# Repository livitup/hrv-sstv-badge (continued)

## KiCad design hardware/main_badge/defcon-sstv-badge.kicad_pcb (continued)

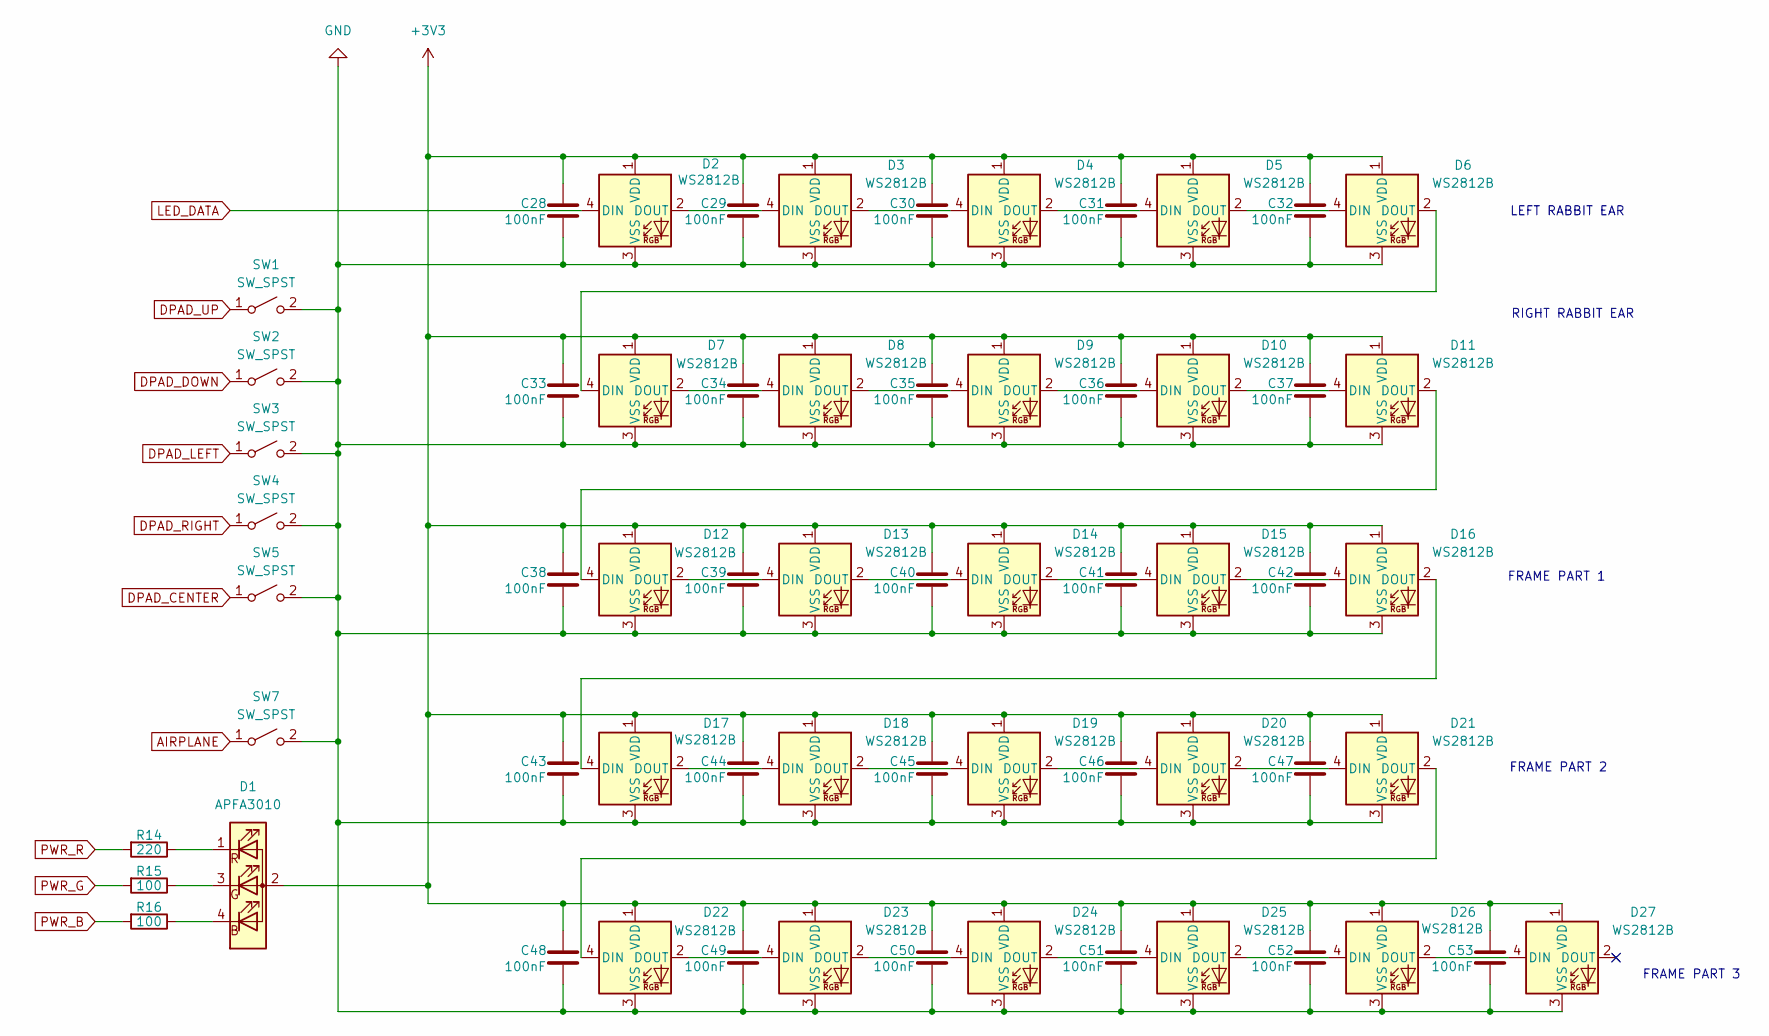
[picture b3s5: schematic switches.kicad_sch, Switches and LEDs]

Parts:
C28, C29, C30, C31, C32, C33, C34, C35, C36, C37, C38, C39, C40, C41, C42, C43, C44, C45, C46, C47, C48, C49, C50, C51, C52, C53: 100nF; C_0402_1005Metric
D1: APFA3010; LED_Kingbright_APFA3010_3x1.5mm_Horizontal
D2, D3, D4, D5, D6, D7, D8, D9, D10, D11: WS2812B; LED_WS2812B_PLCC4_5.0x5.0mm_P3.2mm
D12, D13, D14, D15, D16, D17, D18, D19, D20, D21, D22, D23, D24, D25, D26, D27: WS2812B; LED_WS2812B-2020_PLCC4_2.0x2.0mm
R14: 220; R_0603_1608Metric
R15, R16: 100; R_0603_1608Metric
SW1, SW2, SW3, SW4, SW5: SW_SPST; SW_PUSH_6mm_H5mm
SW7: SW_SPST; SW_Slide_SPDT_Angled_CK_OS102011MA1Q

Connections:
+3V3: C28.1, C29.1, C30.1, C31.1, C32.1, C33.1, C34.1, C35.1, C36.1, C37.1, C38.1, C39.1, C40.1, C41.1, C42.1, C43.1, C44.1, C45.1, C46.1, C47.1, C48.1, C49.1, C50.1, C51.1, C52.1, C53.1, D1.2 (A), D2.1 (VDD), D3.1 (VDD), D4.1 (VDD), D5.1 (VDD), D6.1 (VDD), D7.1 (VDD), D8.1 (VDD), D9.1 (VDD), D10.1 (VDD), D11.1 (VDD), D12.1 (VDD), D13.1 (VDD), D14.1 (VDD), D15.1 (VDD), D16.1 (VDD), D17.1 (VDD), D18.1 (VDD), D19.1 (VDD), D20.1 (VDD), D21.1 (VDD), D22.1 (VDD), D23.1 (VDD), D24.1 (VDD), D25.1 (VDD), D26.1 (VDD), D27.1 (VDD); also elsewhere on the board
AIRPLANE: SW7.1 (A); also elsewhere on the board
DPAD_CENTER: SW5.1 (A); also elsewhere on the board
DPAD_DOWN: SW2.1 (A); also elsewhere on the board
DPAD_LEFT: SW3.1 (A); also elsewhere on the board
DPAD_RIGHT: SW4.1 (A); also elsewhere on the board
DPAD_UP: SW1.1 (A); also elsewhere on the board
LED_DATA: D2.4 (DIN); also elsewhere on the board
unnamed: D1.4 (B), R16.1
unnamed: D1.3 (G), R15.1
unnamed: D1.1 (R), R14.1
unnamed: D2.2 (DOUT), D3.4 (DIN)
unnamed: D3.2 (DOUT), D4.4 (DIN)
unnamed: D4.2 (DOUT), D5.4 (DIN)
unnamed: D5.2 (DOUT), D6.4 (DIN)
unnamed: D6.2 (DOUT), D7.4 (DIN)
unnamed: D7.2 (DOUT), D8.4 (DIN)
unnamed: D8.2 (DOUT), D9.4 (DIN)
unnamed: D9.2 (DOUT), D10.4 (DIN)
unnamed: D10.2 (DOUT), D11.4 (DIN)
unnamed: D11.2 (DOUT), D12.4 (DIN)
unnamed: D12.2 (DOUT), D13.4 (DIN)
unnamed: D13.2 (DOUT), D14.4 (DIN)
unnamed: D14.2 (DOUT), D15.4 (DIN)
unnamed: D15.2 (DOUT), D16.4 (DIN)
unnamed: D16.2 (DOUT), D17.4 (DIN)
unnamed: D17.2 (DOUT), D18.4 (DIN)
unnamed: D18.2 (DOUT), D19.4 (DIN)
unnamed: D19.2 (DOUT), D20.4 (DIN)
unnamed: D20.2 (DOUT), D21.4 (DIN)
unnamed: D21.2 (DOUT), D22.4 (DIN)
unnamed: D22.2 (DOUT), D23.4 (DIN)
unnamed: D23.2 (DOUT), D24.4 (DIN)
unnamed: D24.2 (DOUT), D25.4 (DIN)
unnamed: D25.2 (DOUT), D26.4 (DIN)
unnamed: D26.2 (DOUT), D27.4 (DIN)
PWR_B: R16.2; also elsewhere on the board
PWR_G: R15.2; also elsewhere on the board
PWR_R: R14.2; also elsewhere on the board

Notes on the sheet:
FRAME PART 2
FRAME PART 3
LEFT RABBIT EAR
FRAME PART 1
RIGHT RABBIT EAR

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
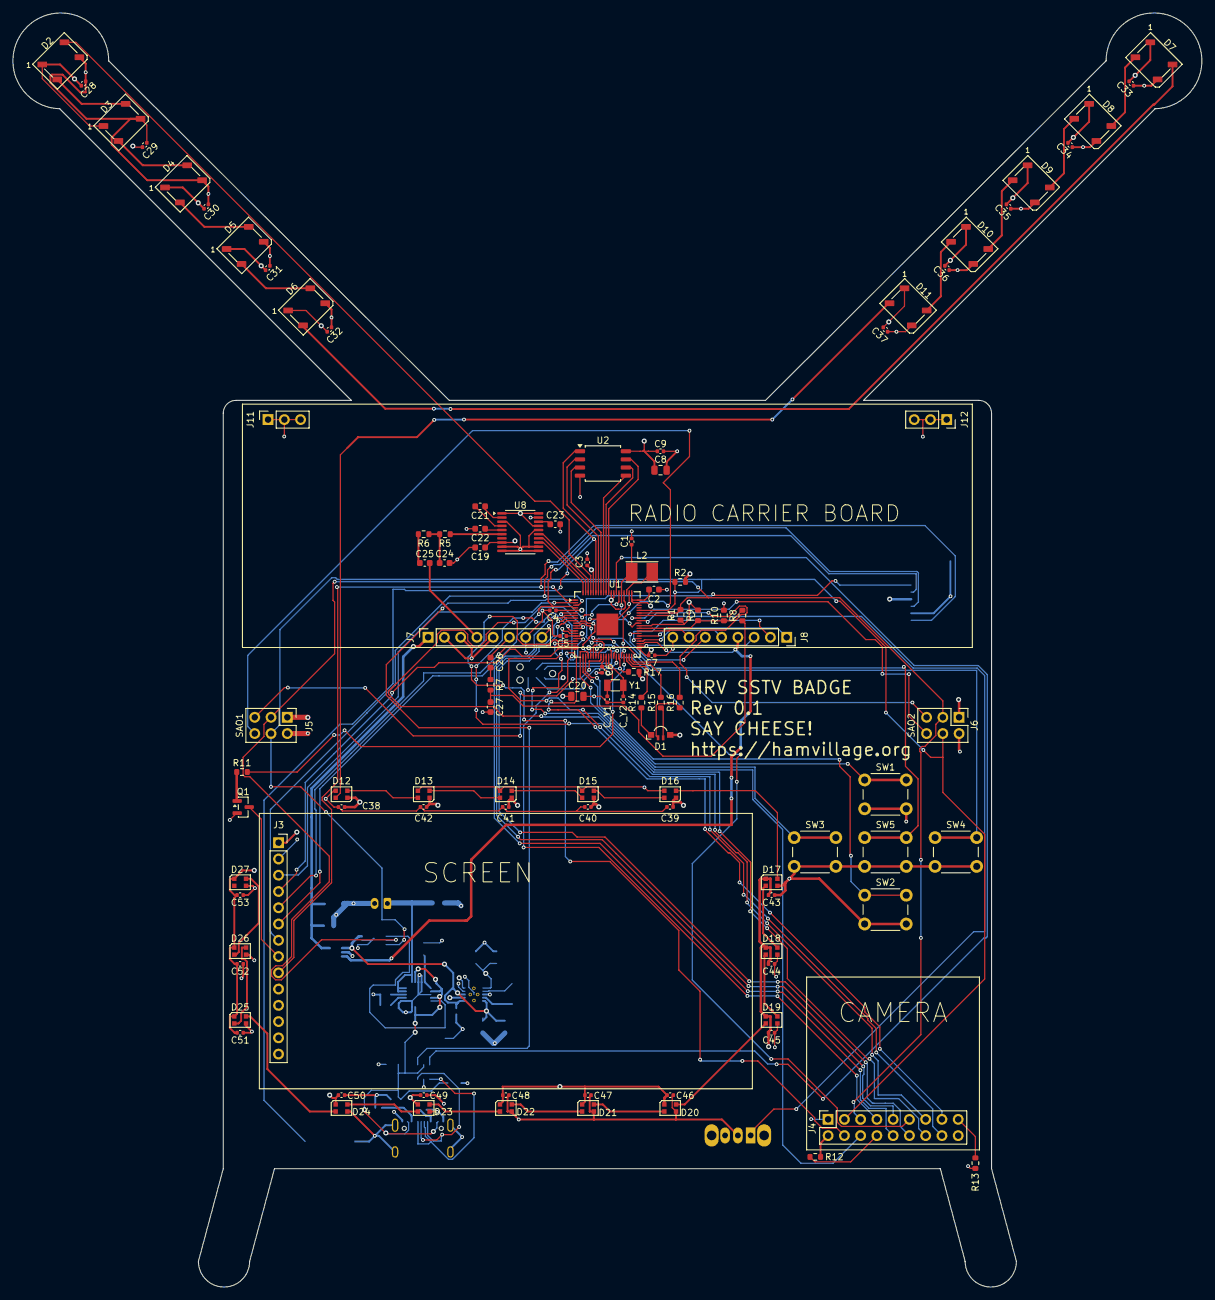
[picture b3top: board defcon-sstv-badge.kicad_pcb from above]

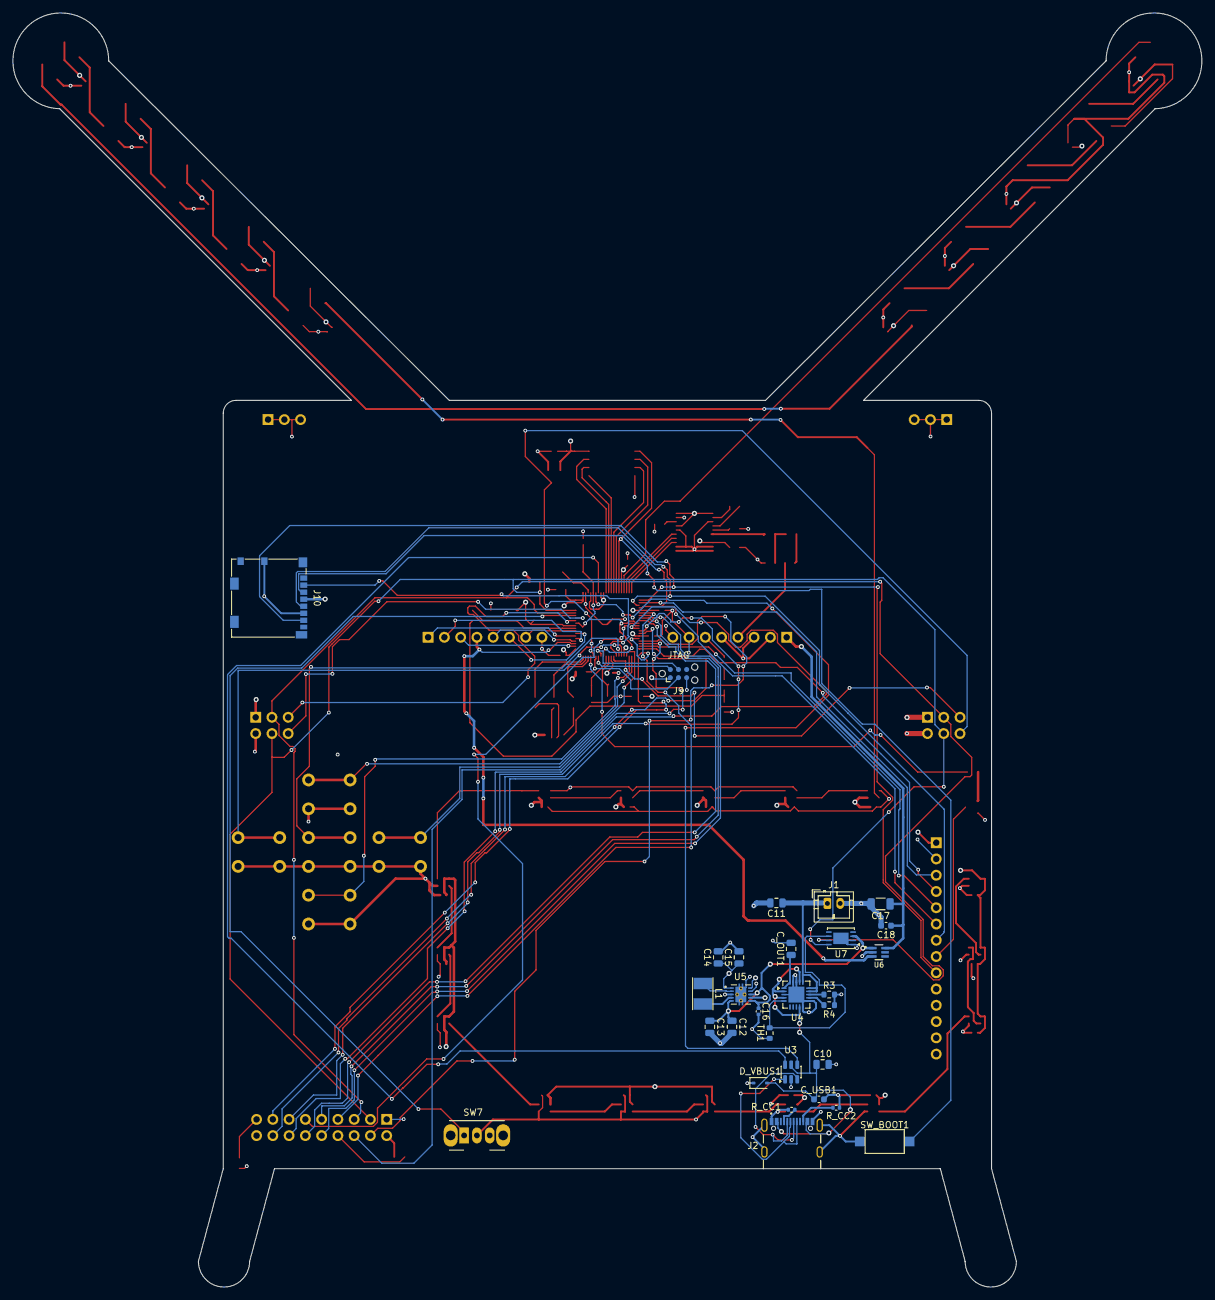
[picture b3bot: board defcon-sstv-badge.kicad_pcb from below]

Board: 4 copper layers, 185.7 x 199.0 mm, 136 parts (29 on the bottom side), 120 nets.

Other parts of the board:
C19, C23, C25: 100nF; C_0603_1608Metric
C20: 10uF; C_0805_2012Metric
C21, C22: 2.2uF; C_0603_1608Metric
C24: 10nF; C_0603_1608Metric
C26: 1uF; C_0603_1608Metric
C27: 4.7nF; C_0603_1608Metric
R5, R9, R10: 47k; R_0603_1608Metric
R6: 470; R_0603_1608Metric
R7, R8: 4.7k; R_0603_1608Metric
U8: PCM5102A; TSSOP-20_4.4x6.5mm_P0.65mm

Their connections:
+3V3: C19.1, C20.1, R9.1, U8.1 (CPVDD), U8.8 (AVDD), U8.17 (XSMT), U8.20 (DVDD); also elsewhere on the board
I2S_BCK: U8.13 (BCK); also elsewhere on the board
I2S_DIN: U8.14 (DIN); also elsewhere on the board
I2S_LRCK: U8.15 (LRCK); also elsewhere on the board
MIC+: C25.2; also elsewhere on the board
unnamed: C24.1, R5.2, R6.1
unnamed: C25.1, R6.2
unnamed: C26.2, R7.1
unnamed: C27.1, R7.2, R8.1
unnamed: C21.2, U8.4 (CAPM)
unnamed: C21.1, U8.2 (CAPP)
unnamed: C23.1, U8.18 (LDOO)
unnamed: R5.1, U8.6 (OUTL)
unnamed: C22.1, U8.5 (VNEG)
RX_AUDIO: R8.2, R9.2, R10.1; also elsewhere on the board
SPK+: C26.1; also elsewhere on the board

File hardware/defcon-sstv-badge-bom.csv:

"Reference","Qty","Value","DNP","Exclude from BOM","Exclude from Board","Footprint","Datasheet"
"C1,C26","2","1uF","","","","","~"
"C2,C8,C10,C11,C12,C13,C14,C15,C18,C20,C55,C57,C_OUT1,C_USB1","14","10uF","","","","","~"
"C3,C4,C5,C6,C7,C9,C16,C19,C23,C25,C28,C29,C30,C31,C32,C33,C34,C35,C36,C37,C38,C39,C40,C41,C42,C43,C44,C45,C46,C47,C48,C49,C50,C51,C52,C53,C54,C56","38","100nF","","","","","~"
"C17","1","100uF","","","","","~"
"C21,C22","2","2.2uF","","","","","~"
"C24","1","10nF","","","","","~"
"C27","1","4.7nF","","","","","~"
"C_Y1,C_Y2","2","15pF","","","","","~"
"D1","1","APFA3010","","","","LED_SMD:LED_Kingbright_APFA3010_3x1.5mm_Horizontal","http://www.kingbrightusa.com/images/catalog/SPEC/APFA3010LSE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"
"D2,D3,D4,D5,D6,D7,D8,D9,D10,D11,D12,D13,D14,D15,D16,D17,D18,D19,D20,D21,D22,D23,D24,D25,D26,D27","26","WS2812B","","","","LED_SMD:LED_WS2812B_PLCC4_5.0x5.0mm_P3.2mm","https://cdn-shop.adafruit.com/datasheets/WS2812B.pdf"
"D_VBUS1","1","D_TVS","","","","","~"
"J1","1","Conn_01x02","","","","","~"
"J2","1","USB4105-GF-A","","","","USB4105-GF-A:GCT_USB4105-GF-A",""
"J3","1","ILI9341 Display Module","","","","","~"
"J4","1","OV2640 Camera Module","","","","","~"
"J5","1","SAO1","","","","","~"
"J6","1","SAO2","","","","","~"
"J7,J8","2","Conn_01x08_Socket","","","","","~"
"J9","1","Conn_ARM_SWD_TagConnect_TC2030-NL","","Excluded from BOM","","Connector:Tag-Connect_TC2030-IDC-NL_2x03_P1.27mm_Vertical","https://www.tag-connect.com/wp-content/uploads/bsk-pdf-manag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"
"J10","1","Micro_SD_Card","","","","","https://www.we-online.com/components/products/datasheet/6930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"
"J11,J12","2","Mechanical only - N/C","","","","","~"
"J13,J19","2","Conn_Coaxial","","","","","~"
"J14,J18","2","Power/Audio","","","","","~"
"J15,J20","2","Control/Data","","","","","~"
"J16,J17,J21,J22","4","Conn_01x03_Pin","","","","","~"
"L1","1","1uH","","","","","~"
"L2","1","3.3uH","","","","","~"
"Q1","1","2N7002","","","","Package_TO_SOT_SMD:SOT-23","https://www.onsemi.com/pub/Collateral/NDS7002A-D.PDF"
"R1,R2,R7,R8","4","4.7k","","","","","~"
"R3","1","2k","","","","","~"
"R4","1","15k","","","","","~"
"R5,R9,R10","3","47k","","","","","~"
"R6","1","470","","","","","~"
"R11","1","1k","","","","","~"
"R12,R13,R17","3","10k","","","","","~"
"R14","1","220","","","","","~"
"R15,R16","2","100","","","","","~"
"R18","1","0","","","","","~"
"R_CC1,R_CC2","2","5.1k","","","","","~"
"SW1,SW2,SW3,SW4,SW5,SW6,SW7","7","SW_SPST","","","","","~"
"SW_BOOT1","1","SW_Push","","","","","~"
"TH1","1","NTC 10k","","","","","~"
"U1","1","RP2350B","","","","Package_DFN_QFN:QFN-80-1EP_10x10mm_P0.4mm_EP3.4x3.4mm","https://datasheets.raspberrypi.com/rp2350/rp2350-datasheet.pdf"
"U2","1","W25Q128JVS","","","","Package_SO:SOIC-8_5.3x5.3mm_P1.27mm","https://www.winbond.com/resource-files/w25q128jv_dtr%20revc%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"
"U3","1","USBLC6-2SC6","","","","Package_TO_SOT_SMD:SOT-23-6","https://www.st.com/resource/en/datasheet/usblc6-2.pdf"
"U4","1","MCP73871","","","","Package_DFN_QFN:QFN-20-1EP_4x4mm_P0.5mm_EP2.5x2.5mm","http://www.mouser.com/ds/2/268/22090a-52174.pdf"
"U5","1","TPS63001DRCR","","","","TPS63001DRCR:VREG_V62_16624-01YE",""
"U6","1","TPS22919DCKT","","","","TPS22919DCKT:SOT65P210X110-6N",""
"U7","1","LC709203FQH-01TWG","","","","Package_DFN_QFN:WDFN-8-1EP_4x3mm_P0.65mm_EP2.4x1.8mm","https://www.onsemi.com/download/data-sheet/pdf/lc709203f-d.pdf"
"U8","1","PCM5102A","","","","Package_SO:TSSOP-20_4.4x6.5mm_P0.65mm","https://www.ti.com/lit/ds/symlink/pcm5102a.pdf"
"U9","1","SA818V","","","","VHF_UHF_Modules:VHF_UHF_Module_generic",""
"U10","1","SA818U","","","","VHF_UHF_Modules:VHF_UHF_Module_generic",""
"Y1","1","12MHz","","","","","~"

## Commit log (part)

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2025-09-02 Initial commit, full documentation suite
2025-09-02 Add claude context
2025-09-04 Update documentation
2025-09-04 Update build defaults
2025-09-04 add details on non-ham lockdown and V/UHF swap
2025-09-04 add details to context about SSTV timing requirements and core usage and updated make defaults
2026-02-07 Update all the documentation.
2026-02-08 ignore autosave
2026-02-08 ignore autosave maybe for real
2026-02-08 mcu power layout
2026-02-08 add oscilator
2026-02-08 add flash reader
2026-02-08 ignore kicad backup files
2026-02-08 add bootloader switch
2026-02-08 add I2C pullups
2026-02-09 add charging controller
2026-02-09 add buck/boost
2026-02-09 add TPS22919 for powering off the radio
2026-02-09 add battery fuel gauge
2026-02-09 RX Filter
2026-02-09 TX Filter pt. 2
2026-02-10 camera/display sheet
2026-02-10 Buttons and LEDs
2026-02-11 MCP GPIO pins to labels
2026-02-16 all design sheets complete, ERC clean
2026-02-16 add BOM
2026-02-16 update BOM and documentation
2026-02-16 add carrier boards for SA818 modules
2026-02-16 add raw BOM
2026-02-16 split documentation between notebook and final state docs
2026-02-16 add footprints and break carrier boards out into standalone projects
2026-02-17 vhf board layout
2026-03-16 VHF Carrier Board
2026-03-16 UHF carrier board
2026-03-16 move main badge files to subdirectory
2026-03-22 main board done except for placing LEDs and drawing ears... I think
2026-03-22 screen LEDs placed, photo button removed
2026-03-23 main badge final updates
2026-03-23 documentation update
2026-03-23 update text on carrier boards
2026-03-23 update the PCB for tv cabinet feet
2026-03-23 documentation updates
2026-03-23 add routing docs
2026-03-23 inital power cap placement
2026-03-23 most of the load capacitors
2026-03-25 USB port and chip routed
2026-03-25 U5 routing complete
2026-03-29 work in progress power subsystems routing
2026-03-31 traces all fubar, might delete them all and start over.
2026-04-01 clean PCB, prior to rewiring for clean board design
2026-04-01 updated MCU pin layout
2026-04-27 wip routing
2026-04-27 more routing, 29 to go...
2026-05-01 routing. 2 nodes to go...
2026-05-01 all traces complete, but lots of DRC warnings to fix
2026-05-01 connect J7 pin 8 to GND
2026-05-01 routing and component bug fixes
2026-05-10 main board finished, no DRC errors
